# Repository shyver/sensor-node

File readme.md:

# Battery-Powered ESP32 Environmental Sensor Node

## Overview

This project is a compact, battery-powered environmental monitoring device built around the ESP32. It is designed to measure temperature, humidity, and atmospheric pressure, and transmit data wirelessly over Wi-Fi.

The system integrates power management, battery charging, sensing, and communication into a single PCB, making it suitable for IoT applications and embedded product prototyping.

---

## Features

* ESP32-based Wi-Fi connectivity
* Environmental sensing (temperature, humidity, pressure)
* Battery-powered operation (Li-Po)
* USB-C power input and charging
* Integrated battery protection
* Low-power design (deep sleep capable)
* UART interface for programming and debugging

---

## Hardware Architecture

The system is composed of the following main subsystems:

### Power Subsystem

* USB-C 5V input
* Li-Po battery charging IC
* Battery protection circuit
* 3.3V regulation stage
* Bulk and decoupling capacitors

### Processing Unit

* ESP32-WROOM-32 module
* Boot configuration and reset circuitry
* UART programming interface

### Sensor Subsystem

* BME280 environmental sensor (I2C interface)
* Pull-up resistors for I2C communication

---

## Block Diagram

```
USB-C → Charger → Battery → Regulator → ESP32 → Sensor (I2C)
```

---

## Design Highlights

* Modular schematic organization (power / MCU / sensor)
* Proper decoupling and power distribution
* ESP32 antenna keep-out respected
* I2C bus design with pull-up resistors
* Battery protection and safe charging design

---

## Key Engineering Decisions

* **ESP32 Module Selection**
  Used a pre-certified ESP32 module to simplify RF design and ensure reliable Wi-Fi performance.

* **Battery-Powered Architecture**
  Designed around a single-cell Li-Po battery for portability and real-world IoT use cases.

* **Power Regulation Strategy**
  Implemented a regulated 3.3V rail to ensure stable operation during ESP32 current spikes.

* **USB-C Power-Only Configuration**
  USB-C connector used strictly for power input, avoiding unnecessary USB data complexity.

* **I2C Sensor Interface**
  Selected a digital sensor with I2C to minimize pin usage and simplify routing.

---

## PCB Design

* 2-layer PCB
* Ground plane for signal integrity
* Compact component placement
* Standard SMD components (0603 passives)
* Connector placement optimized for usability

---

## Files Included

### Design Files

* Schematic files
* PCB layout files

### Manufacturing Files

* Gerbers
* Drill files
* Bill of Materials (BOM)
* Pick-and-place files

### Documentation

* Block diagram
* Rendered board images

---

## Applications

* IoT environmental monitoring
* Smart home systems
* Remote sensing nodes
* Battery-powered embedded systems

---

## Future Improvements

* Power path optimization (load sharing / advanced charger IC)
* Lower power consumption tuning
* OTA firmware update support
* Enclosure design integration
* Additional sensor support

---

## Author

Hardware design and layout by Abdelwahed Eloued

---

## License

This project is open-source and available under the MIT License.

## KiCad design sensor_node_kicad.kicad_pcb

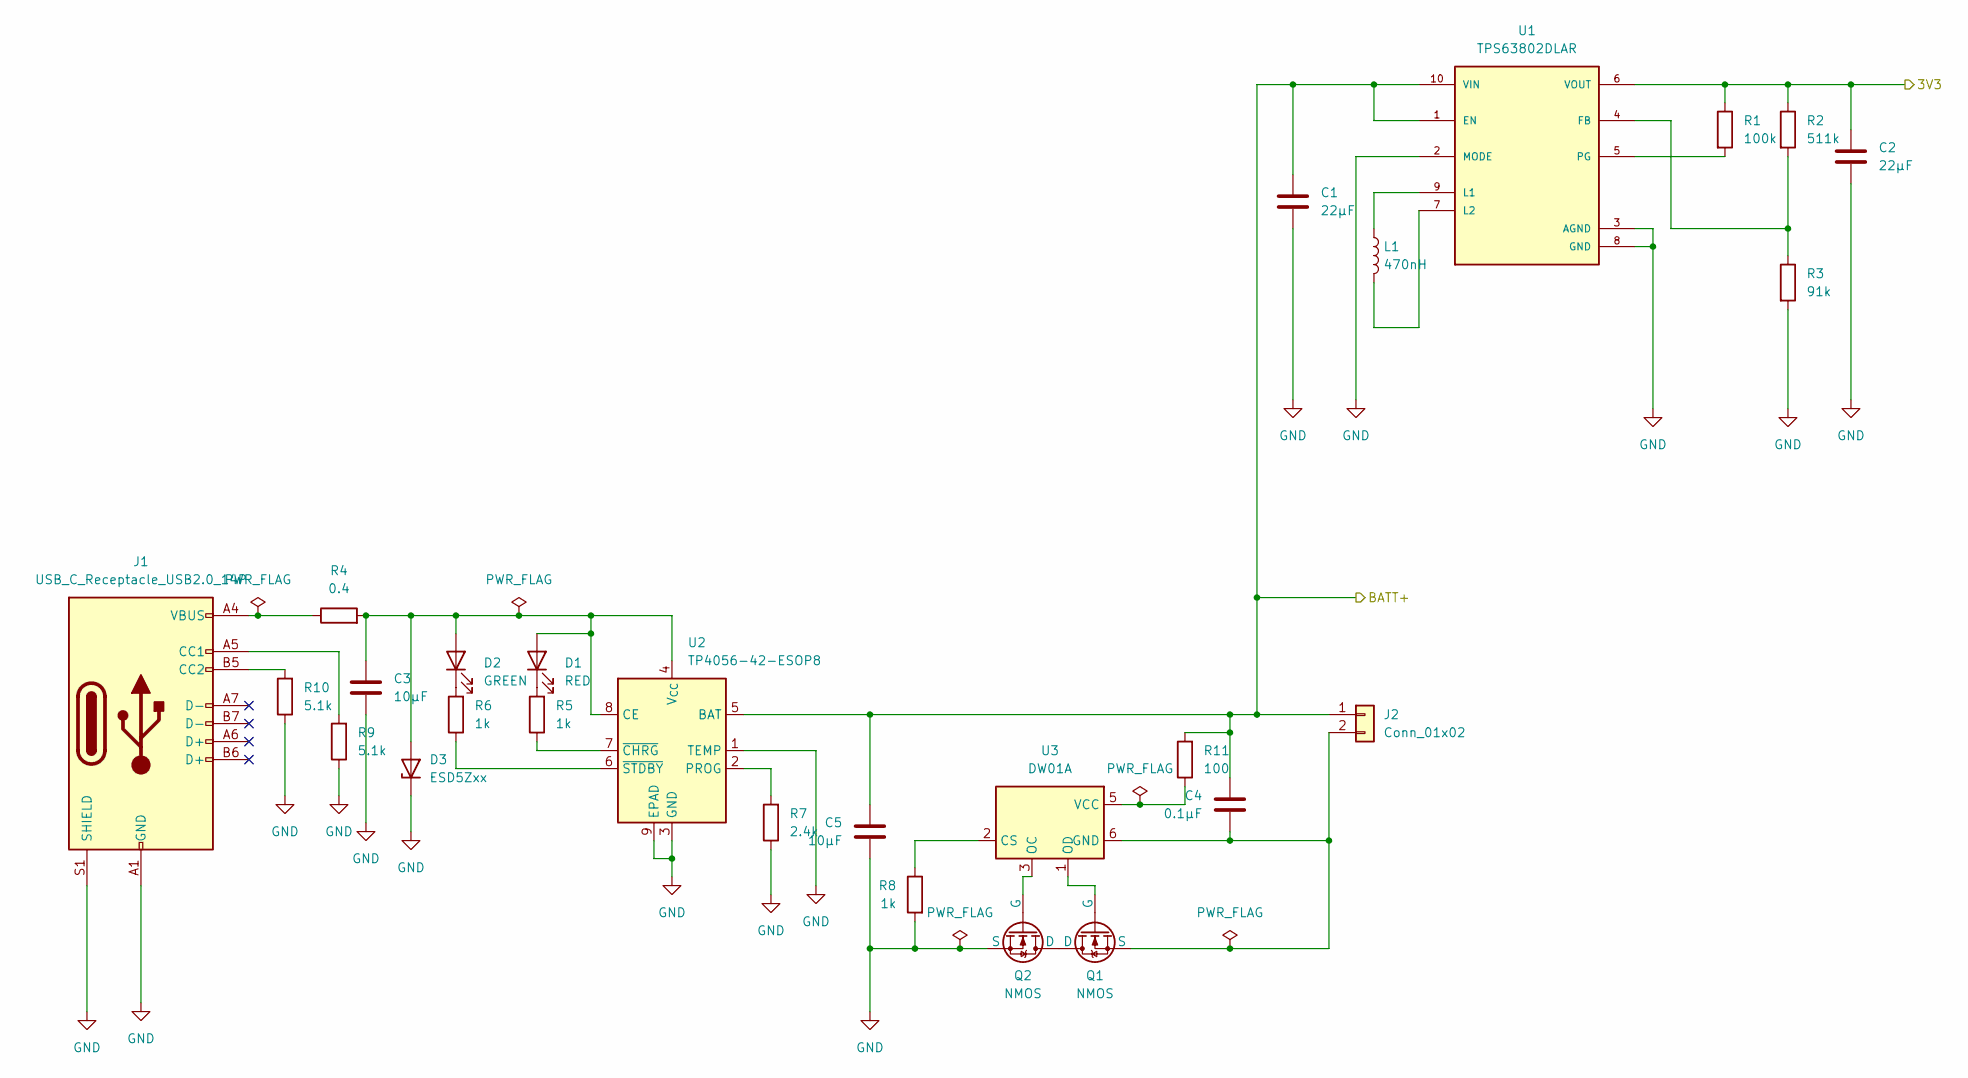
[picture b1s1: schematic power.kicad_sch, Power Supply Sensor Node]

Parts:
C1, C2: 22µF; C_0805_2012Metric
C3, C5: 10µF; C_0805_2012Metric
C4: 0.1µF; C_0603_1608Metric
D1: RED; LED_0603_1608Metric
D2: GREEN; LED_0603_1608Metric
D3: ESD5Zxx; D_SOD-523
J1: USB_C_Receptacle_USB2.0_14P; USB_C_Receptacle_GCT_USB4085
J2: Conn_01x02; JST_PH_S2B-PH-SM4-TB_1x02-1MP_P2.00mm_Horizontal
L1: 470nH; IND_XFL4015_COC-M
Q1, Q2: NMOS; SOT-23
R1: 100k; R_0603_1608Metric
R2: 511k; R_0603_1608Metric
R3: 91k; R_0603_1608Metric
R4: 0.4; R_0603_1608Metric
R5, R6, R8: 1k; R_0603_1608Metric
R7: 2.4k; R_0603_1608Metric
R9, R10: 5.1k; R_0603_1608Metric
R11: 100; R_0603_1608Metric
U1: TPS63802DLAR; VREG_TPS63802DLAR; PARTREV B
U2: TP4056-42-ESOP8; SOIC-8-1EP_3.9x4.9mm_P1.27mm_EP2.41x3.3mm_ThermalVias
U3: DW01A; SOT-23-6

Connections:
/Power/3V3: C2.1, R1.1, R2.1, U1.6 (VOUT); also elsewhere on the board
/Power/BATT+: C1.1, C4.2, C5.2, J2.1, R11.2, U1.1 (EN), U1.10 (VIN), U2.5 (BAT); also elsewhere on the board
GND: C1.2, C2.2, C3.2, C5.1, D3.1 (K), J1.A1 (GND), J1.A12 (GND), J1.B1 (GND), J1.B12 (GND), J1.S1 (SHIELD), Q2.3 (S), R3.2, R7.1, R8.2, R9.1, R10.1, U1.2 (MODE), U1.3 (AGND), U1.8 (GND), U2.1 (TEMP), U2.3 (GND), U2.9 (EPAD); also elsewhere on the board
unnamed: C3.1, D1.2 (A), D2.2 (A), D3.2 (A), R4.2, U2.4 (V_{CC}), U2.8 (CE)
unnamed: D1.1 (K), R5.2
unnamed: D2.1 (K), R6.2
unnamed: J1.A5 (CC1), R9.2
unnamed: J1.B5 (CC2), R10.2
unnamed: J1.A4 (VBUS), J1.A9 (VBUS), J1.B4 (VBUS), J1.B9 (VBUS), R4.1
unnamed: C4.1, J2.2, Q1.3 (S), U3.6 (GND)
unnamed: Q1.1 (D), Q2.1 (D)
unnamed: Q1.2 (G), U3.1 (OD)
unnamed: Q2.2 (G), U3.3 (OC)
unnamed: R2.2, R3.1, U1.4 (FB)
unnamed: L1.1, U1.9 (L1)
unnamed: L1.2, U1.7 (L2)
unnamed: R1.2, U1.5 (PG)
unnamed: R7.2, U2.2 (PROG)
unnamed: R5.1, U2.7 (~CHRG)
unnamed: R6.1, U2.6 (~STDBY)
unnamed: R8.1, U3.2 (CS)
unnamed: R11.1, U3.5 (VCC)

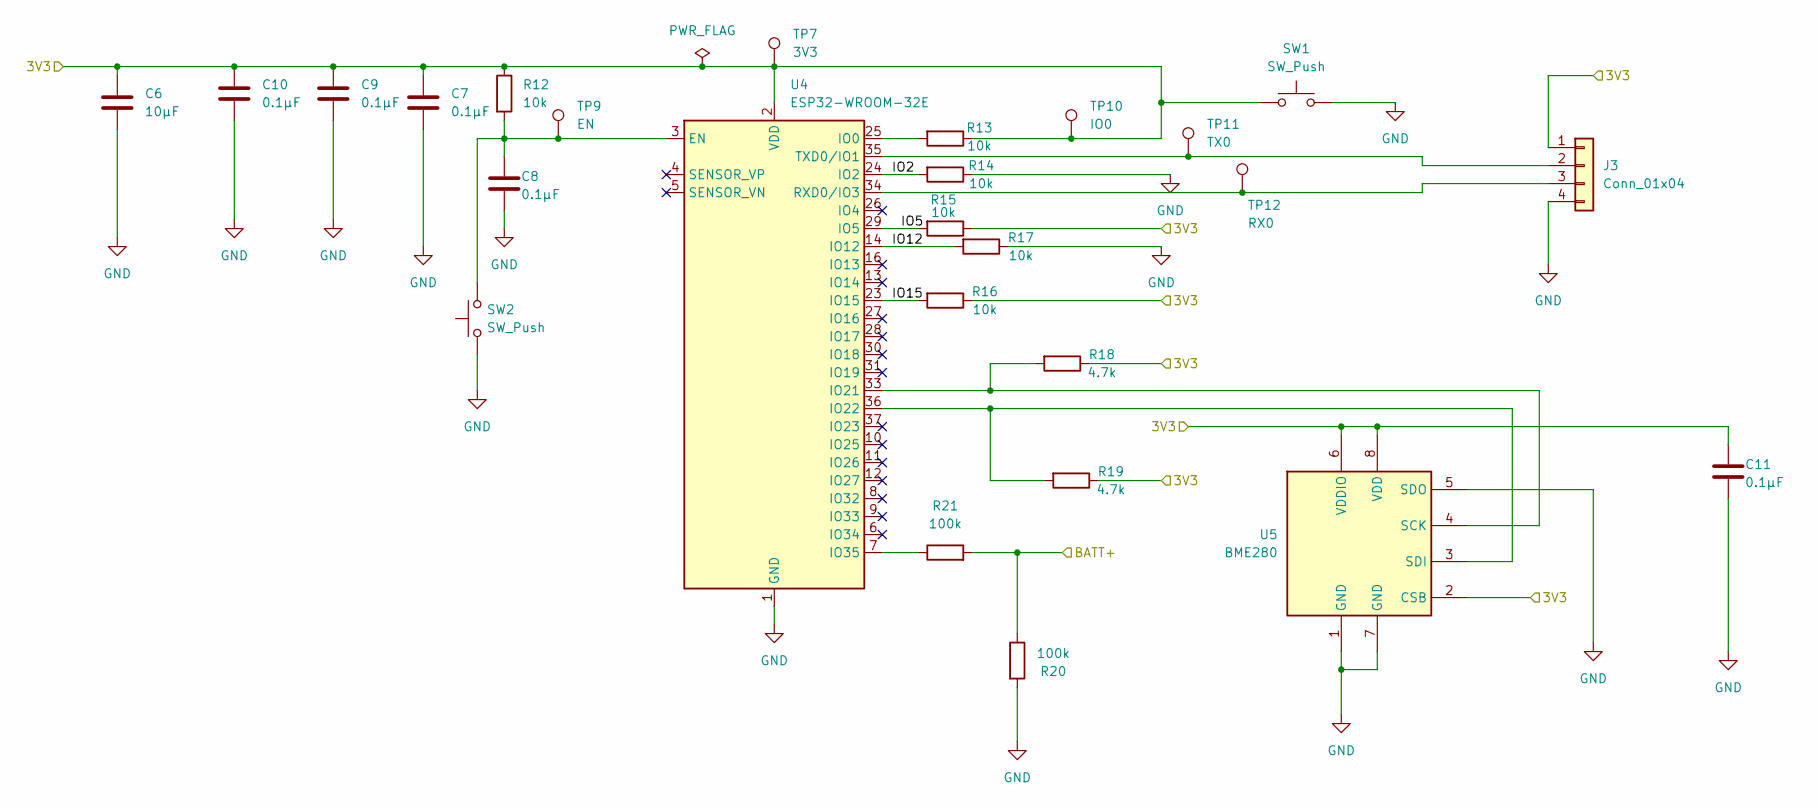
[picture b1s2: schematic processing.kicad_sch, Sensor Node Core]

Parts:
C6: 10µF; C_0805_2012Metric
C7, C8, C9, C10, C11: 0.1µF; C_0603_1608Metric
J3: Conn_01x04; PinHeader_1x04_P2.54mm_Vertical
R12, R13, R14, R15, R16, R17: 10k; R_0603_1608Metric
R18, R19: 4.7k; R_0603_1608Metric
R20, R21: 100k; R_0603_1608Metric
SW1, SW2: SW_Push; SW_SPST_TL3342
TP7: 3V3; TestPoint_Pad_D1.5mm
TP9: EN; TestPoint_Pad_D1.5mm
TP10: IO0; TestPoint_Pad_D1.5mm
TP11: TX0; TestPoint_Pad_D1.5mm
TP12: RX0; TestPoint_Pad_D1.5mm
U4: ESP32-WROOM-32E; ESP32-WROOM-32D
U5: BME280; Bosch_LGA-8_2.5x2.5mm_P0.65mm_ClockwisePinNumbering

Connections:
/Power/3V3: C6.1, C7.1, C9.1, C10.1, C11.1, J3.1, R12.1, R13.1, R15.1, R16.1, R18.1, R19.1, SW1.1, TP7.1, TP10.1, U4.2 (VDD), U5.2 (CSB), U5.6 (VDDIO), U5.8 (VDD); also elsewhere on the board
/Power/BATT+: R20.1, R21.2; also elsewhere on the board
/Sensor Node Core/IO2: R14.2, U4.24 (IO2)
/Sensor Node Core/IO5: R15.2, U4.29 (IO5)
/Sensor Node Core/IO12: R17.2, U4.14 (IO12)
/Sensor Node Core/IO15: R16.2, U4.23 (IO15)
GND: C6.2, C7.2, C8.2, C9.2, C10.2, C11.2, J3.4, R14.1, R17.1, R20.2, SW1.2, SW2.1, U4.1 (GND), U4.15 (GND), U4.38 (GND), U4.39 (GND), U5.1 (GND), U5.5 (SDO), U5.7 (GND); also elsewhere on the board
unnamed: J3.2, TP11.1, U4.35 (TXD0/IO1)
unnamed: J3.3, TP12.1, U4.34 (RXD0/IO3)
unnamed: C8.1, R12.2, SW2.2, TP9.1, U4.3 (EN)
unnamed: R13.2, U4.25 (IO0)
unnamed: R18.2, U4.33 (IO21), U5.4 (SCK)
unnamed: R19.2, U4.36 (IO22), U5.3 (SDI)
unnamed: R21.1, U4.7 (IO35)

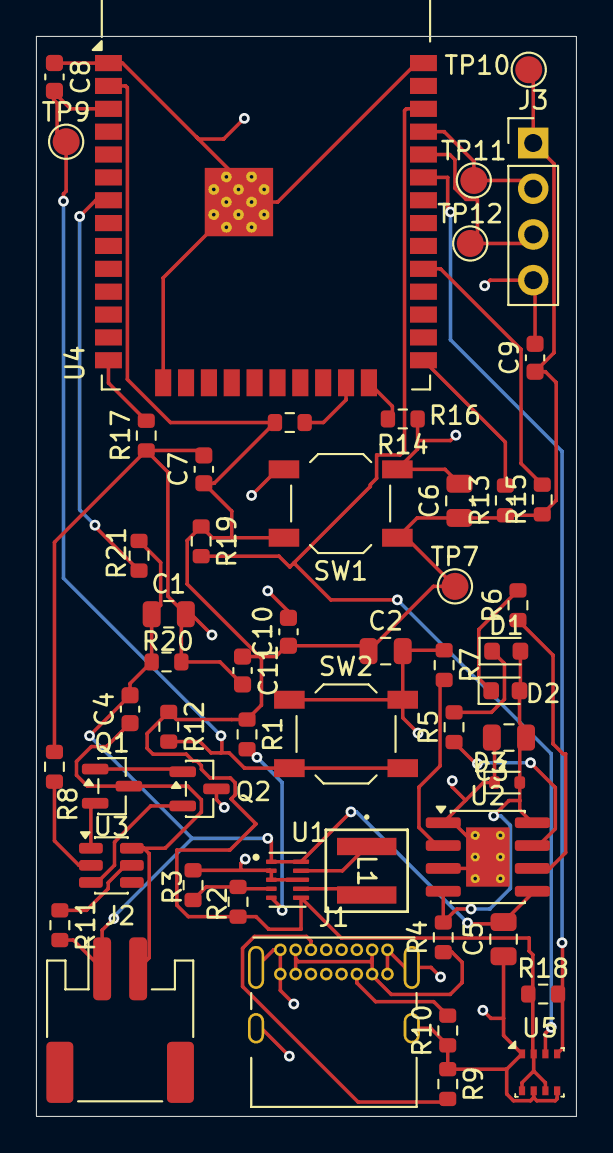
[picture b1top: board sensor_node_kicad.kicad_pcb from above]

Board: 2 copper layers, 30.0 x 60.0 mm, 53 parts (0 on the bottom side), 33 nets.

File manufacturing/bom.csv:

"Reference","Qty","Value","DNP","Exclude from BOM","Exclude from Board","Footprint","Datasheet"
"C1,C2","2","22µF","","","","Capacitor_SMD:C_0805_2012Metric","~"
"C3,C5,C6","3","10µF","","","","Capacitor_SMD:C_0805_2012Metric","~"
"C4,C7,C8,C9,C10,C11","6","0.1µF","","","","Capacitor_SMD:C_0603_1608Metric","~"
"D1","1","RED","","","","LED_SMD:LED_0603_1608Metric","~"
"D2","1","GREEN","","","","LED_SMD:LED_0603_1608Metric","~"
"D3","1","ESD5Zxx","","","","Diode_SMD:D_SOD-523","https://www.onsemi.com/pdf/datasheet/esd5z2.5t1-d.pdf"
"J1","1","USB_C_Receptacle_USB2.0_14P","","","","Connector_USB:USB_C_Receptacle_GCT_USB4085","https://www.usb.org/sites/default/files/documents/usb_type-c.zip"
"J2","1","Conn_01x02","","","","Connector_JST:JST_PH_S2B-PH-SM4-TB_1x02-1MP_P2.00mm_Horizontal","~"
"J3","1","Conn_01x04","","","","Connector_PinHeader_2.54mm:PinHeader_1x04_P2.54mm_Vertical","~"
"L1","1","470nH","","","","ul_XFL4015-471MEC:IND_XFL4015_COC-M","~"
"Q1,Q2","2","NMOS","","","","Package_TO_SOT_SMD:SOT-23","https://ngspice.sourceforge.io/docs/ngspice-html-manual/manu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"
"R1,R20,R21","3","100k","","","","Resistor_SMD:R_0603_1608Metric","~"
"R2","1","511k","","","","Resistor_SMD:R_0603_1608Metric","~"
"R3","1","91k","","","","Resistor_SMD:R_0603_1608Metric","~"
"R4","1","0.4","","","","Resistor_SMD:R_0603_1608Metric","~"
"R5,R6,R8","3","1k","","","","Resistor_SMD:R_0603_1608Metric","~"
"R7","1","2.4k","","","","Resistor_SMD:R_0603_1608Metric","~"
"R9,R10","2","5.1k","","","","Resistor_SMD:R_0603_1608Metric","~"
"R11","1","100","","","","Resistor_SMD:R_0603_1608Metric","~"
"R12,R13,R14,R15,R16,R17","6","10k","","","","Resistor_SMD:R_0603_1608Metric","~"
"R18,R19","2","4.7k","","","","Resistor_SMD:R_0603_1608Metric","~"
"SW1,SW2","2","SW_Push","","","","Button_Switch_SMD:SW_SPST_TL3342","~"
"TP7","1","3V3","","","","TestPoint:TestPoint_Pad_D1.5mm","~"
"TP9","1","EN","","","","TestPoint:TestPoint_Pad_D1.5mm","~"
"TP10","1","IO0","","","","TestPoint:TestPoint_Pad_D1.5mm","~"
"TP11","1","TX0","","","","TestPoint:TestPoint_Pad_D1.5mm","~"
"TP12","1","RX0","","","","TestPoint:TestPoint_Pad_D1.5mm","~"
"U1","1","TPS63802DLAR","","","","TPS63802DLAR:VREG_TPS63802DLAR",""
"U2","1","TP4056-42-ESOP8","","","","Package_SO:SOIC-8-1EP_3.9x4.9mm_P1.27mm_EP2.41x3.3mm_ThermalVias","https://www.lcsc.com/datasheet/lcsc_datasheet_2410121619_TOP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"
"U3","1","DW01A","","","","Package_TO_SOT_SMD:SOT-23-6","https://hmsemi.com/downfile/DW01A.PDF"
"U4","1","ESP32-WROOM-32E","","","","RF_Module:ESP32-WROOM-32D","https://www.espressif.com/sites/default/files/documentation/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"
"U5","1","BME280","","","","Package_LGA:Bosch_LGA-8_2.5x2.5mm_P0.65mm_ClockwisePinNumbering","https://www.bosch-sensortec.com/media/boschsensortec/downloa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"

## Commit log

2026-03-19 progressed in the processing unit, BME280 still needs proper implementation
2026-03-19 completed the sensor node core (esp32 and the sensor chip)
2026-03-19 finalized the schematic design
2026-03-19 finalized layout
2026-03-19 added metadata
2026-03-20 added readme file
2026-03-20 Update author name in README
2026-03-20 Add MIT License to the project
2026-03-20 added manufacturing files
2026-03-20 added media
2026-03-20 added schematic pdf
2026-03-20 Remove 'Design notes' from documentation section
